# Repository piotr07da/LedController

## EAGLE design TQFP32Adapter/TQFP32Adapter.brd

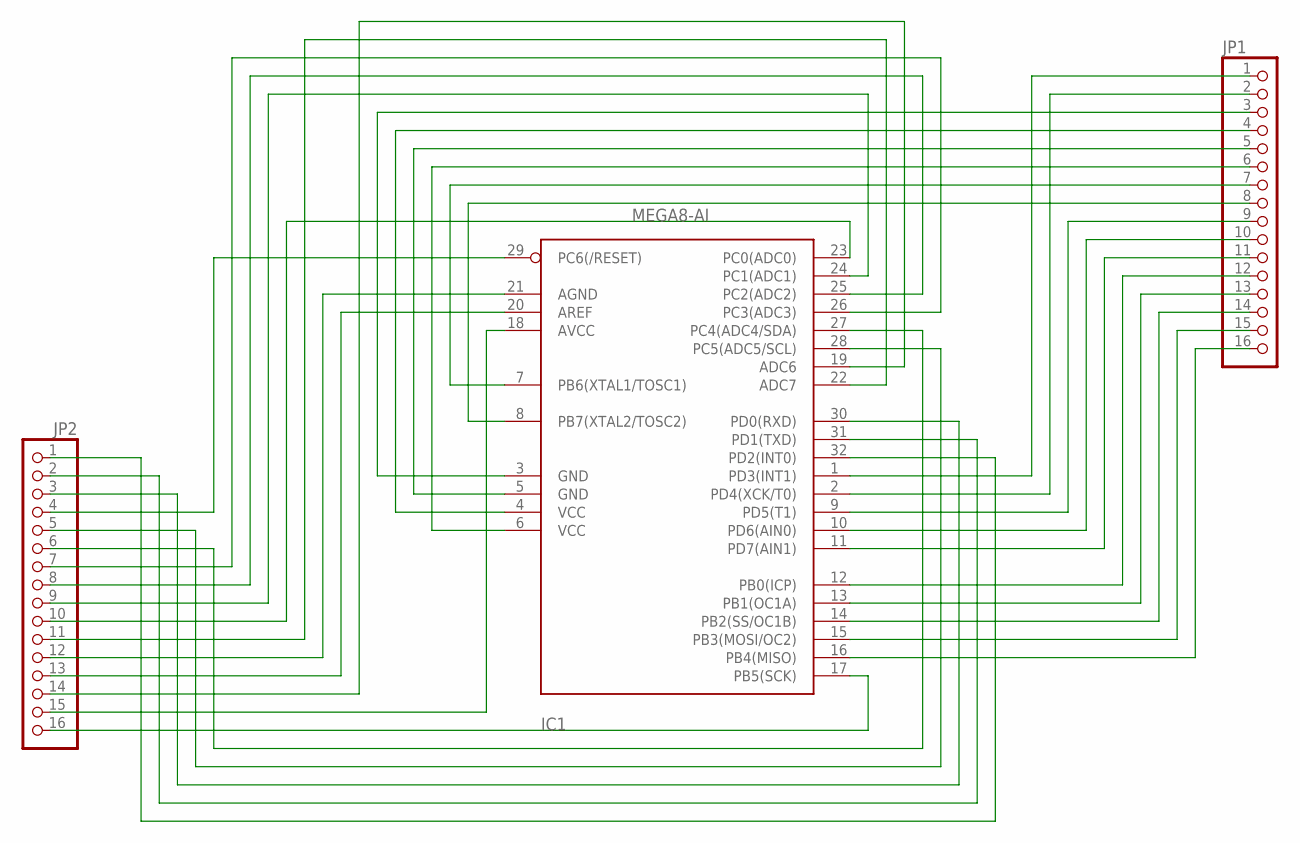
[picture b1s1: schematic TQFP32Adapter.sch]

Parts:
IC1: MEGA8-AI; TQFP32-08
JP1, JP2: PINHD-1X16; 1X16

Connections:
unnamed: IC1.1 (PD3(INT1)), JP1.1
unnamed: IC1.2 (PD4(XCK/T0)), JP1.2
unnamed: IC1.3 (GND), JP1.3
unnamed: IC1.4 (VCC), JP1.4
unnamed: IC1.5 (GND), JP1.5
unnamed: IC1.6 (VCC), JP1.6
unnamed: IC1.7 (PB6(XTAL1/TOSC1)), JP1.7
unnamed: IC1.8 (PB7(XTAL2/TOSC2)), JP1.8
unnamed: IC1.9 (PD5(T1)), JP1.9
unnamed: IC1.10 (PD6(AIN0)), JP1.10
unnamed: IC1.11 (PD7(AIN1)), JP1.11
unnamed: IC1.12 (PB0(ICP)), JP1.12
unnamed: IC1.13 (PB1(OC1A)), JP1.13
unnamed: IC1.14 (PB2(SS/OC1B)), JP1.14
unnamed: IC1.15 (PB3(MOSI/OC2)), JP1.15
unnamed: IC1.16 (PB4(MISO)), JP1.16
unnamed: IC1.17 (PB5(SCK)), JP2.16
unnamed: IC1.18 (AVCC), JP2.15
unnamed: IC1.19 (ADC6), JP2.14
unnamed: IC1.20 (AREF), JP2.13
unnamed: IC1.21 (AGND), JP2.12
unnamed: IC1.22 (ADC7), JP2.11
unnamed: IC1.23 (PC0(ADC0)), JP2.10
unnamed: IC1.24 (PC1(ADC1)), JP2.9
unnamed: IC1.25 (PC2(ADC2)), JP2.8
unnamed: IC1.26 (PC3(ADC3)), JP2.7
unnamed: IC1.27 (PC4(ADC4/SDA)), JP2.6
unnamed: IC1.28 (PC5(ADC5/SCL)), JP2.5
unnamed: IC1.29 (PC6(/RESET)), JP2.4
unnamed: IC1.30 (PD0(RXD)), JP2.3
unnamed: IC1.31 (PD1(TXD)), JP2.2
unnamed: IC1.32 (PD2(INT0)), JP2.1

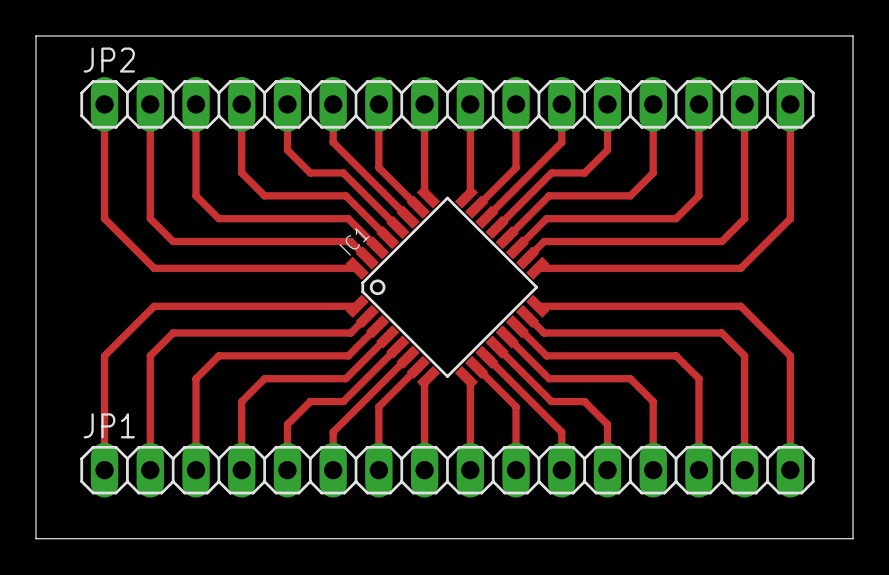
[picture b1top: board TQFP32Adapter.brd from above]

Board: 2 copper layers, 45.4 x 27.9 mm, 3 parts (0 on the bottom side), 32 nets.

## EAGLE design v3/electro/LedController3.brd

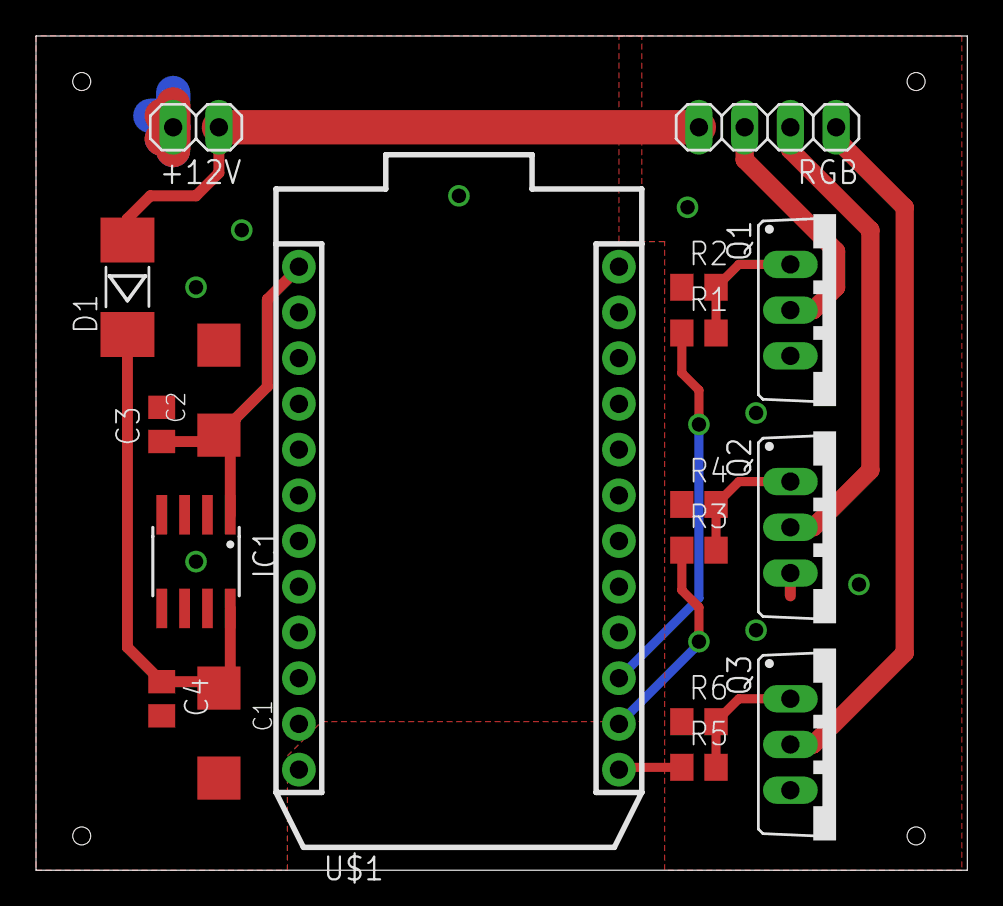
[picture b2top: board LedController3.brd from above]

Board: 2 copper layers, 51.7 x 46.3 mm, 18 parts (0 on the bottom side), 13 nets.

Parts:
+12V: 2pin; 1X02
C1, C2: 10u; SMC_C
C3, C4: 100n; C0805
D1: SM4004; MELF-MLL41
IC1: L78L05ABD; SO08
Q1, Q2, Q3: IRL2703PBF; TO220BV
R1, R3, R5: 0; R0805
R2, R4, R6: 28k; R0805
RGB: 4pin; 1X04
U$1: PHOTON_WITH_HEADERS; PHOTON

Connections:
+5V: C2.+, C3.1, IC1.1, U$1.1
+12V: +12V.1, D1.A, RGB.4
B-: Q3.D, RGB.1
G-: Q2.D, RGB.2
GND: +12V.2, C1.-, C2.-, C3.2, C4.2, IC1.2, IC1.3, IC1.6, IC1.7, Q1.S, Q2.S, Q3.S, R2.1, R4.1, R6.1, U$1.2, U$1.21
unnamed: C1.+, C4.1, D1.C, IC1.8
unnamed: Q3.G, R5.2, R6.2
unnamed: Q2.G, R3.2, R4.2
unnamed: Q1.G, R1.2, R2.2
PWM_B: R5.1, U$1.13
PWM_G: R3.1, U$1.14
PWM_R: R1.1, U$1.15
R-: Q1.D, RGB.3

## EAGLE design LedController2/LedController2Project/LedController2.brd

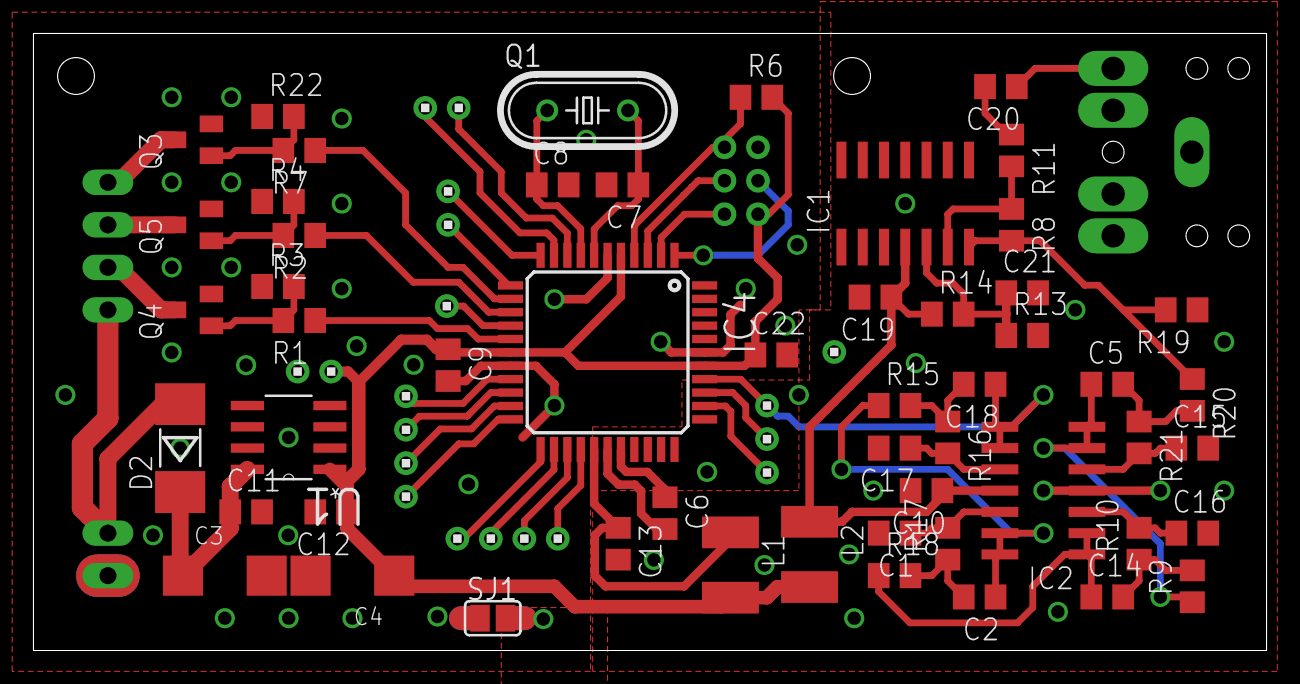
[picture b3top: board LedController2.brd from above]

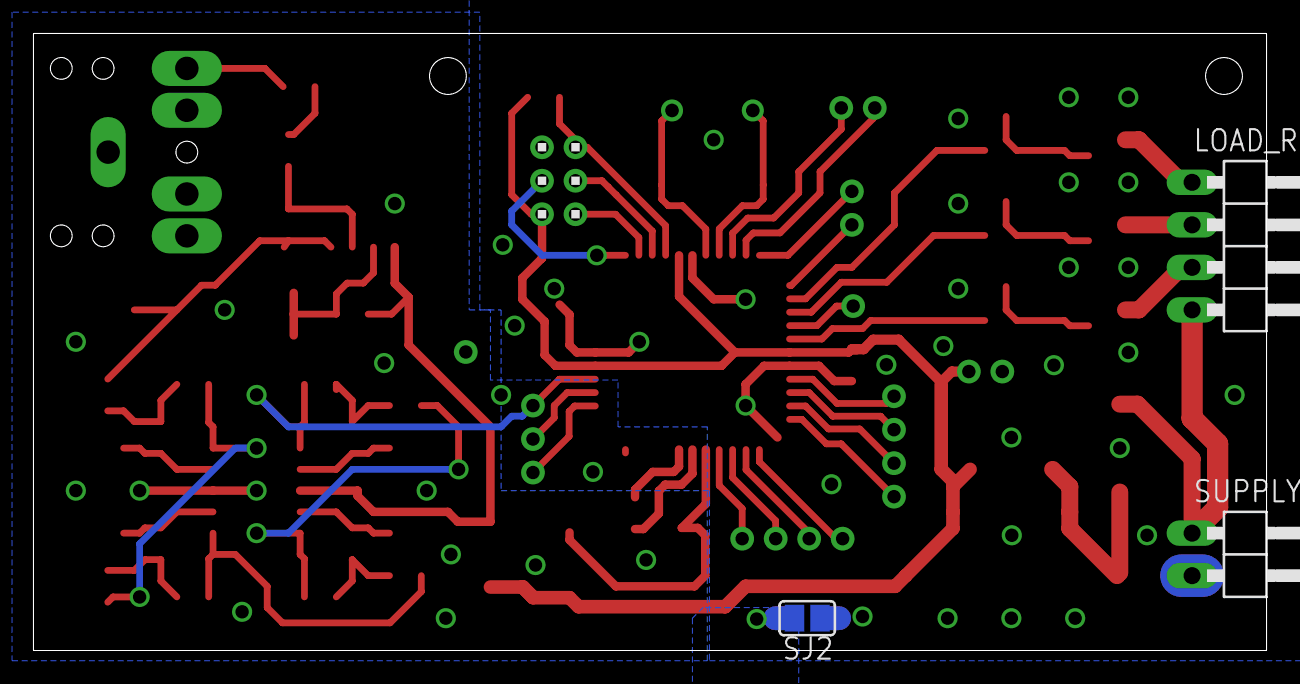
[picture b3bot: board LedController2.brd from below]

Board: 2 copper layers, 73.7 x 36.9 mm, 67 parts (4 on the bottom side), 55 nets.

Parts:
AUDIO: 1X3
AUDIO_GND: 1X1
C1, C15, C16, C17: 2.2n; C0805
C2: 0.47u; C0805
C3, C4: 10u; SMC_C
C5: 10n; C0805
C6, C9, C10, C11, C12, C13, C14, C19, C22: 100n; C0805
C7, C8: 15p; C0805
C18: 4.7u; C0805
C20, C21: 10u; C0805
D2: SM4004; MELF-MLL41
IC1, IC2: LM324D; SO14
IC4: MEGA32-A; TQFP44
INNER_SUPPLY: 1X2
L1, L2: 10u; L1812
LOAD_RGB: 1X04/90
Q1: 14.7456M-HC49-S; HC49/S
Q3, Q4, Q5: IRLML6344; SOT23
R1, R2, R7: 0; R0805
R3, R4, R22: 28k; R0805
R6, R11: 10k; R0805
R8, R13, R14: 100k; R0805
R9: 2.74k; R0805
R10, R19: 6.49k; R0805
R15: 301; R0805
R16: 412; R0805
R17: 1.91k; R0805
R18: 909; R0805
R20: 26.1k; R0805
R21: 43.2k; R0805
SERIAL, SERIAL1: 1X2
SJ1, SJ2: SJ
SUPPLY: 1X02/90
U1: L78L05ABD; SOIC127P600X175-8N
U$1, U$2: 1X4
U$4: 1X1
U$5: 2X3
U$6: JACK35

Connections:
+5V: C4.+, C9.1, C12.1, C22.1, IC4.5, IC4.17, IC4.38, INNER_SUPPLY.1, L1.2, L2.2, R6.2, U1.1, U$5.2
ADC0: AUDIO.1, C18.1, IC2.8, IC2.9, IC4.37
ADC1: AUDIO.2, IC4.36
ADC2: AUDIO.3, IC4.35
AGND: AUDIO_GND.1, C1.2, C6.2, C10.2, C13.2, C15.2, C16.2, C17.2, C19.2, C21.2, IC1.11, IC2.4, IC4.28, R13.2, R19.1, SJ1.2, SJ2.2, U$6.SHUNT_TERMINAL_A_5, U$6.SHUNT_TERMINAL_B_4, U$6.SLEEVE_3
AREF: C6.1, IC4.29
AVCC: C13.1, IC4.27, L1.1
B-: LOAD_RGB.2, Q5.3
G-: LOAD_RGB.3, Q4.3
GND: C3.-, C4.-, C7.2, C8.2, C9.2, C11.2, C12.2, C22.2, IC4.6, IC4.18, IC4.39, INNER_SUPPLY.2, Q3.2, Q4.2, Q5.2, R3.1, R4.1, R22.1, SJ1.1, SJ2.1, SUPPLY.2, U1.2, U1.3, U1.6, U1.7, U$5.6
unnamed: C20.2, R11.1
unnamed: Q3.1, R7.2, R22.2
unnamed: IC4.3, U$5.3
unnamed: IC4.2, U$5.1
unnamed: Q4.1, R1.2, R3.2
unnamed: C3.+, C11.1, D2.C, U1.8
unnamed: IC1.7, R8.2, R19.2, R20.1
unnamed: C14.2, R9.2, R10.1
unnamed: Q5.1, R2.2, R4.2
unnamed: IC4.1, U$5.4
unnamed: IC1.6, R8.1, R11.2
unnamed: C5.1, IC2.6, IC2.7, R9.1
unnamed: C10.1, C19.1, IC1.4, IC2.11, L2.1, R14.1
unnamed: C21.1, IC1.5, R13.1, R14.2
unnamed: C15.1, IC2.5, R21.2
unnamed: C16.1, IC2.3, R10.2
unnamed: C17.1, IC2.10, R16.2
unnamed: C2.1, IC2.13, IC2.14, R15.1
unnamed: C5.2, R20.2, R21.1
unnamed: C18.2, R15.2, R16.1
unnamed: C14.1, IC2.1, IC2.2, R18.1
unnamed: C1.1, IC2.12, R17.2
unnamed: C2.2, R17.1, R18.2
unnamed: C20.1, U$6.TIP_7
unnamed: IC4.22, U$1.4
unnamed: IC4.21, U$1.3
unnamed: IC4.20, U$1.2
unnamed: IC4.19, U$1.1
unnamed: IC4.23, U$2.4
unnamed: IC4.24, U$2.3
unnamed: IC4.25, U$2.2
unnamed: IC4.26, U$2.1
unnamed: IC4.15, U$4.1
PD2: IC4.11, SERIAL1.2
PD3: IC4.12, SERIAL1.1
PWM_LED_B: IC4.14, R2.1
PWM_LED_G: IC4.16, R1.1
PWM_LED_R: IC4.13, R7.1
R-: LOAD_RGB.1, Q3.3
RESET: IC4.4, R6.1, U$5.5
RXD: IC4.9, SERIAL.1
TXD: IC4.10, SERIAL.2
VCC_IN: D2.A, LOAD_RGB.4, SUPPLY.1
XTAL1: C8.1, IC4.8, Q1.1
XTAL2: C7.1, IC4.7, Q1.2

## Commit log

2017-12-31 init
2018-04-20 LedController3 - Particle Photon - schemat i płytka skończone, wygenerowane pliki gerber - wysłane do produkcji do JLCPCB; oraz zalążek kodu na Photon'a
2018-04-22 działający ColorTimeLine, działające wysterowanie PWM, prawidłowe przejścia kolorów
2018-04-23 uzupełnione implementacje w klasie ColorTimeLine potrzebne do zarządzania time linem z aplikacji klienckiej + mały refactor
2018-04-26 porządki
2018-04-29 przerobienie ColorTimePoint.Time z uint8_t na float. Time progress także jako float. Aplikacja kliencka - skończone wyświetlanie - do zrobienia obsługa touch + komunikacja + slidery RGB i progress
2018-04-29 suwak czasu i suwaki sliderów - działające - kominikujące wywołujące i odbierające dane z fake communicatora
2018-05-06 Wersja zaawansowana - klient + photon. Działająca komunikacja z Desktop i Mobile(Android). Fajnie działające suwaki.
2018-05-09 Klient - silniczek komponentów
2018-05-09 color picker - dwie implementacje
2018-05-10 dalsze prace nad HV color pickerem
2018-05-12 doprowadzamy kolor do ładu - potrzeba poprawienia generowania gradient circle po przerobieniu na rysowanie przy pomocy DrawVertices
2018-05-12 no i gradient circle działa, szkoda tylko, że antyaliasing nie działa dla metody DrawVertices
2018-05-13 walka z tcp communicatorem + kolejne poprawki do interpolacji kolorów + kolejne zmiany w hsv color pickerze
2018-05-15 działający HSV color picker + poprawa wydajności - zrobienie mini sliniczka odpalającego z zadanym frame rate'em InvalidateSurface
2022-01-20 LedController2 - kicad
